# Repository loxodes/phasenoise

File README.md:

# low(ish) phase noise downconverter 
* 10-6000 MHz RF
* DC-1MHz IF
* Internal LO generation, phase locked to RF input
* Designed to fit on the J40 header of Lattice ECP5 EVN eval board

Software development and hardware testing is in progress.
The only documentation is the [schematic](./phase_noise_downconver_schematic_2020_10.pdf).

## Usage
This project is under development, y'all probably don't want to try reproducing it yet.

## License
Unless otherwise noted, all work is under a MIT license.

## Contact
Feel free to contact me at arcticmicrowave@gmail.com or loxodes on irc.freenode.net

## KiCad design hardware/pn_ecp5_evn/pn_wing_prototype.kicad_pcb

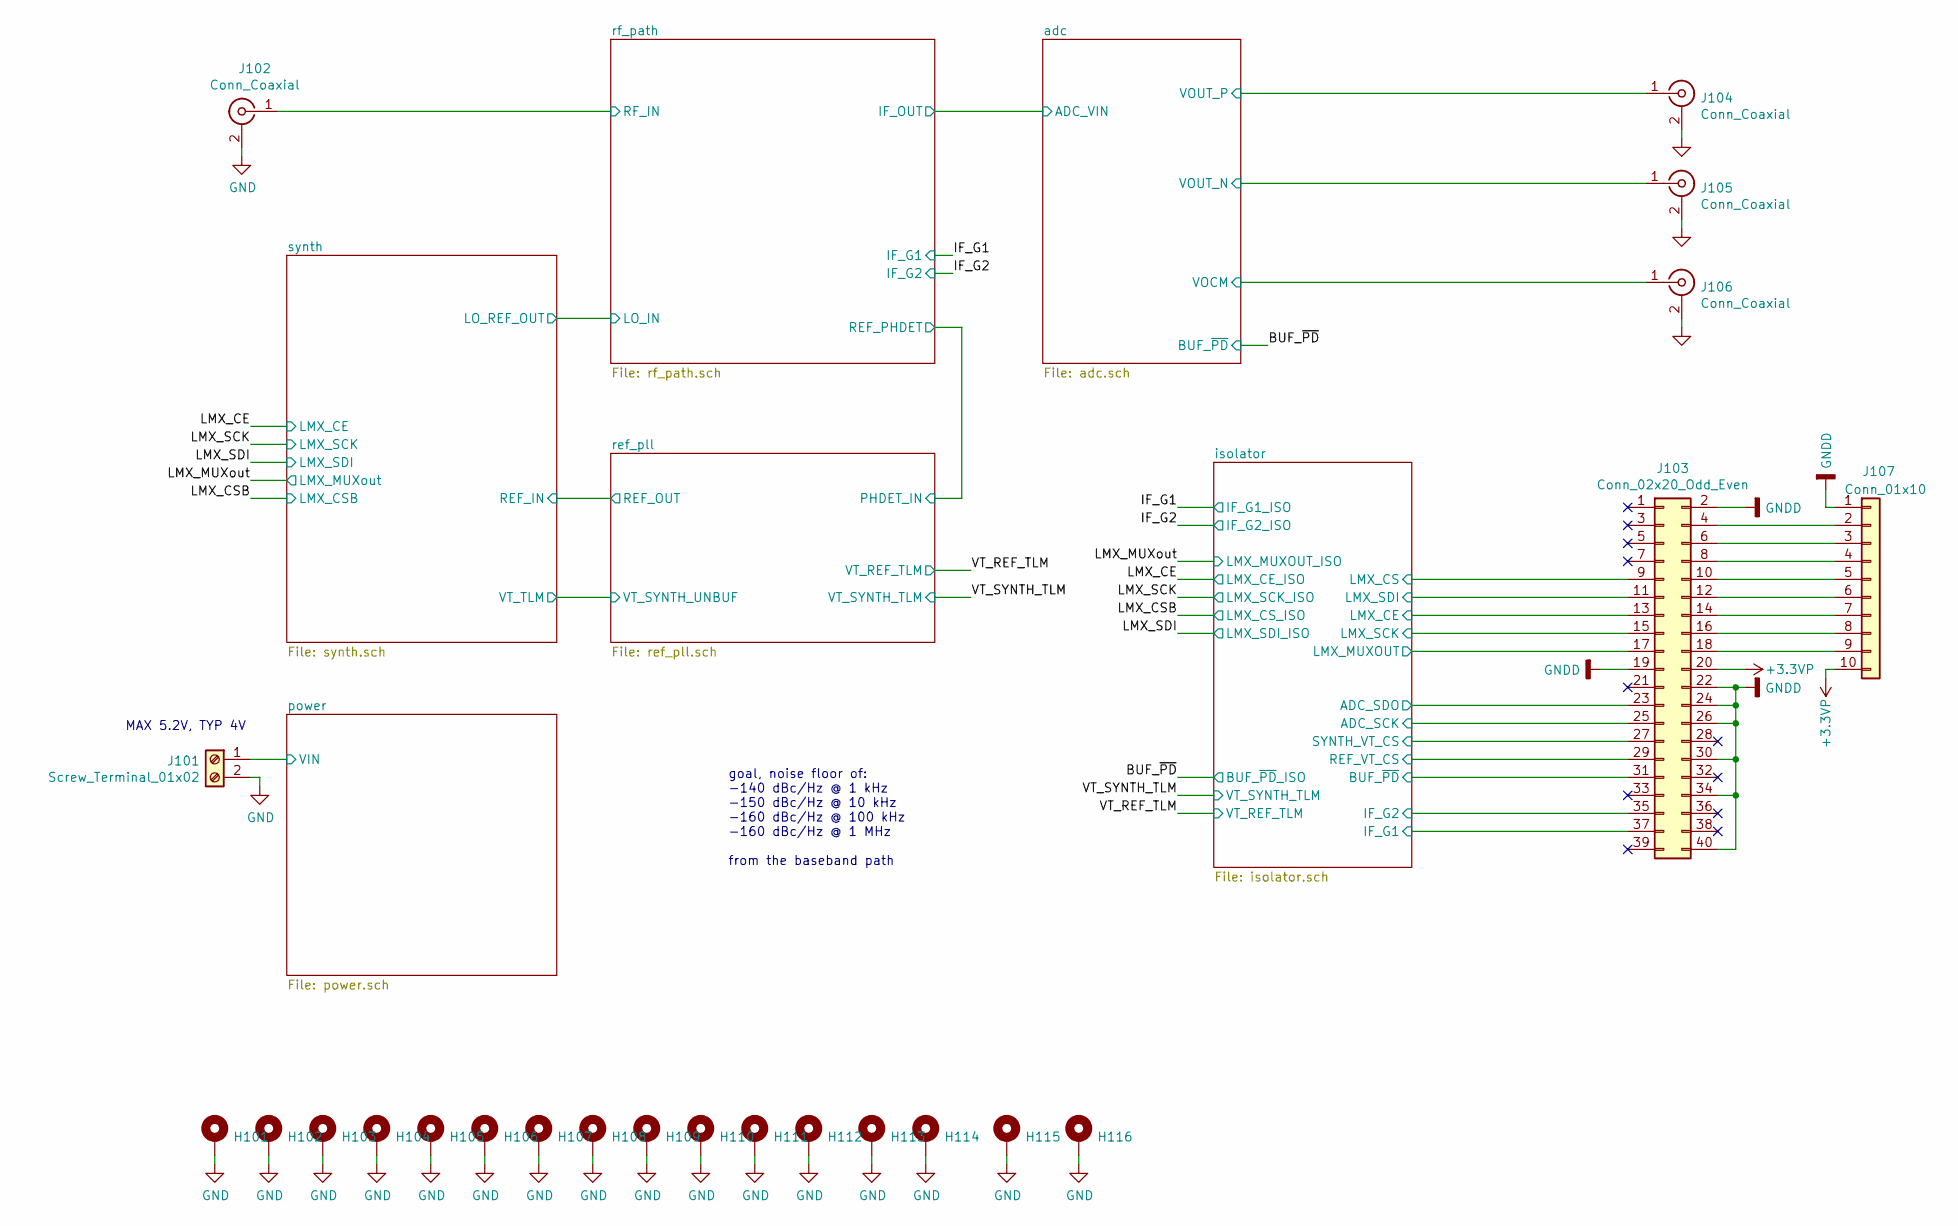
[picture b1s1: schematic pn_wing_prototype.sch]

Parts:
H101, H102, H103, H104, H105, H106, H107, H108, H109, H110, H111, H112, H113, H114, H115, H116: MountingHole_Pad; MountingHole_2.7mm_M2.5_ISO14580_Pad
J101: Screw_Terminal_01x02; TerminalBlock_Phoenix_MPT-0,5-2-2.54_1x02_P2.54mm_Horizontal
J102, J104, J105, J106: Conn_Coaxial; SMA_Molex_73251-1153_OSHFR408
J103: Conn_02x20_Odd_Even; PinSocket_2x20_P2.54mm_Vertical
J107: Conn_01x10; PinHeader_1x10_P2.54mm_Vertical

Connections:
+3.3VP: J103.20, J107.10; also elsewhere on the board
/adc/VOCM: J106.1 (In); also elsewhere on the board
/adc/VOUT_N: J105.1 (In); also elsewhere on the board
/adc/VOUT_P: J104.1 (In); also elsewhere on the board
/isolator/ADC_SCK: J103.25; also elsewhere on the board
/isolator/ADC_SDO: J103.23; also elsewhere on the board
/isolator/BUF_~PD: J103.31; also elsewhere on the board
/isolator/IF_G1: J103.37; also elsewhere on the board
/isolator/IF_G2: J103.35; also elsewhere on the board
/isolator/LMX_CE: J103.13; also elsewhere on the board
/isolator/LMX_CS: J103.9; also elsewhere on the board
/isolator/LMX_MUXOUT: J103.17; also elsewhere on the board
/isolator/LMX_SCK: J103.15; also elsewhere on the board
/isolator/LMX_SDI: J103.11; also elsewhere on the board
/isolator/REF_VT_CS: J103.29; also elsewhere on the board
/isolator/SYNTH_VT_CS: J103.27; also elsewhere on the board
/power/VIN: J101.1; also elsewhere on the board
/rf_path/RF_IN: J102.1 (In); also elsewhere on the board
GND: H101.1, H102.1, H103.1, H104.1, H105.1, H106.1, H107.1, H108.1, H109.1, H110.1, H111.1, H112.1, H113.1, H114.1, H115.1, H116.1, J101.2, J102.2 (Ext), J104.2 (Ext), J105.2 (Ext), J106.2 (Ext); also elsewhere on the board
GNDD: J103.2, J103.19, J103.22, J103.24, J103.26, J103.30, J103.34, J103.40, J107.1; also elsewhere on the board
unnamed: J103.4, J107.2
unnamed: J103.6, J107.3
unnamed: J103.8, J107.4
unnamed: J103.10, J107.5
unnamed: J103.12, J107.6
unnamed: J103.14, J107.7
unnamed: J103.16, J107.8
unnamed: J103.18, J107.9

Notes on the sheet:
goal, noise floor of: -140 dBc/Hz @ 1 kHz -150 dBc/Hz @ 10 kHz -160 dBc/Hz @ 100 kHz -160 dBc/Hz @ 1 MHz from the baseband path
MAX 5.2V, TYP 4V

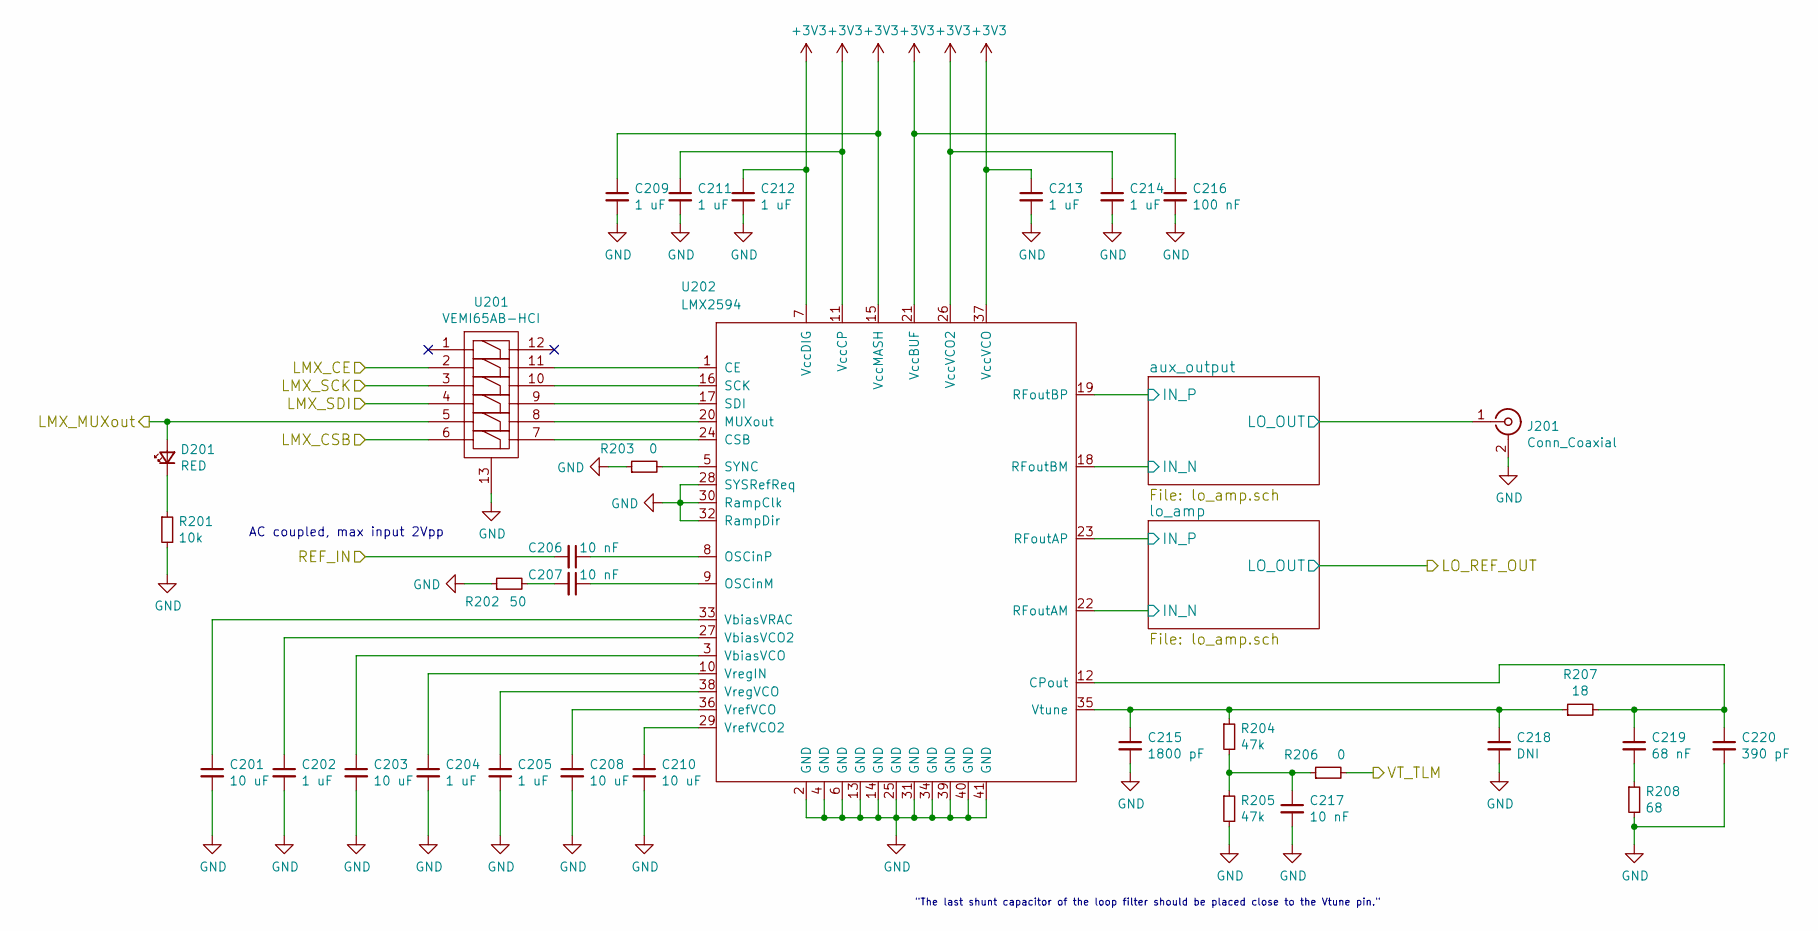
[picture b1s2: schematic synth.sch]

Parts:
C201, C203, C208, C210: 10 uF; C_0603_1608Metric
C202, C204, C205, C209, C211, C212, C213, C214: 1 uF; C_0402_1005Metric
C206, C207, C217: 10 nF; C_0402_1005Metric
C215: 1800 pF; C_0402_1005Metric
C216: 100 nF; C_0402_1005Metric
C218: DNI; C_0603_1608Metric
C219: 68 nF; C_0603_1608Metric
C220: 390 pF; C_0603_1608Metric
D201: RED; LED_0603_1608Metric
J201: Conn_Coaxial; SMA_Molex_73251-1153_OSHFR408
R201: 10k; R_0402_1005Metric
R202: 50; R_0402_1005Metric
R203, R206: 0; R_0402_1005Metric
R204, R205: 47k; R_0402_1005Metric
R207: 18; R_0402_1005Metric
R208: 68; R_0402_1005Metric
U201: VEMI65AB-HCI; LLP2513-13L
U202: LMX2594; Texas_S-PVQFN-N40_EP4.6x4.6mm

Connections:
/LMX_CE: U201.2; also elsewhere on the board
/LMX_CSB: U201.6; also elsewhere on the board
/LMX_MUXout: D201.2 (A), U201.5; also elsewhere on the board
/LMX_SCK: U201.3; also elsewhere on the board
/LMX_SDI: U201.4; also elsewhere on the board
/ref_pll/VT_SYNTH_UNBUF: R206.2; also elsewhere on the board
/synth/REF_IN: C206.2; also elsewhere on the board
/synth/aux_output/IN_N: U202.18 (RFoutBM); also elsewhere on the board
/synth/aux_output/IN_P: U202.19 (RFoutBP); also elsewhere on the board
/synth/aux_output/LO_OUT: J201.1 (In); also elsewhere on the board
/synth/lo_amp/IN_N: U202.22 (RFoutAM); also elsewhere on the board
/synth/lo_amp/IN_P: U202.23 (RFoutAP); also elsewhere on the board
GND: C201.2, C202.2, C203.2, C204.2, C205.2, C208.2, C209.2, C210.2, C211.2, C212.2, C213.2, C214.2, C215.2, C216.2, C217.2, C218.2, C220.2, J201.2 (Ext), R201.2, R202.1, R203.1, R205.2, R208.2, U201.13, U202.2 (GND), U202.4 (GND), U202.6 (GND), U202.13 (GND), U202.14 (GND), U202.25 (GND), U202.28 (SYSRefReq), U202.30 (RampClk), U202.31 (GND), U202.32 (RampDir), U202.34 (GND), U202.39 (GND), U202.40 (GND), U202.41 (GND); also elsewhere on the board
unnamed: C201.1, U202.33 (VbiasVRAC)
unnamed: C202.1, U202.27 (VbiasVCO2)
unnamed: C203.1, U202.3 (VbiasVCO)
unnamed: C204.1, U202.10 (VregIN)
unnamed: C205.1, U202.38 (VregVCO)
unnamed: C206.1, U202.8 (OSCinP)
unnamed: C207.1, U202.9 (OSCinM)
unnamed: C207.2, R202.2
unnamed: C208.1, U202.36 (VrefVCO)
unnamed: C210.1, U202.29 (VrefVCO2)
unnamed: C215.1, C218.1, R204.1, R207.1, U202.35 (Vtune)
unnamed: C217.1, R204.2, R205.1, R206.1
unnamed: C219.1, C220.1, R207.2, U202.12 (CPout)
unnamed: C219.2, R208.1
unnamed: D201.1 (K), R201.1
unnamed: R203.2, U202.5 (SYNC)
unnamed: U201.7, U202.24 (CSB)
unnamed: U201.8, U202.20 (MUXout)
unnamed: U201.9, U202.17 (SDI)
unnamed: U201.10, U202.16 (SCK)
unnamed: U201.11, U202.1 (CE)

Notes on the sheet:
"The last shunt capacitor of the loop filter should be placed close to the Vtune pin."
AC coupled, max input 2Vpp

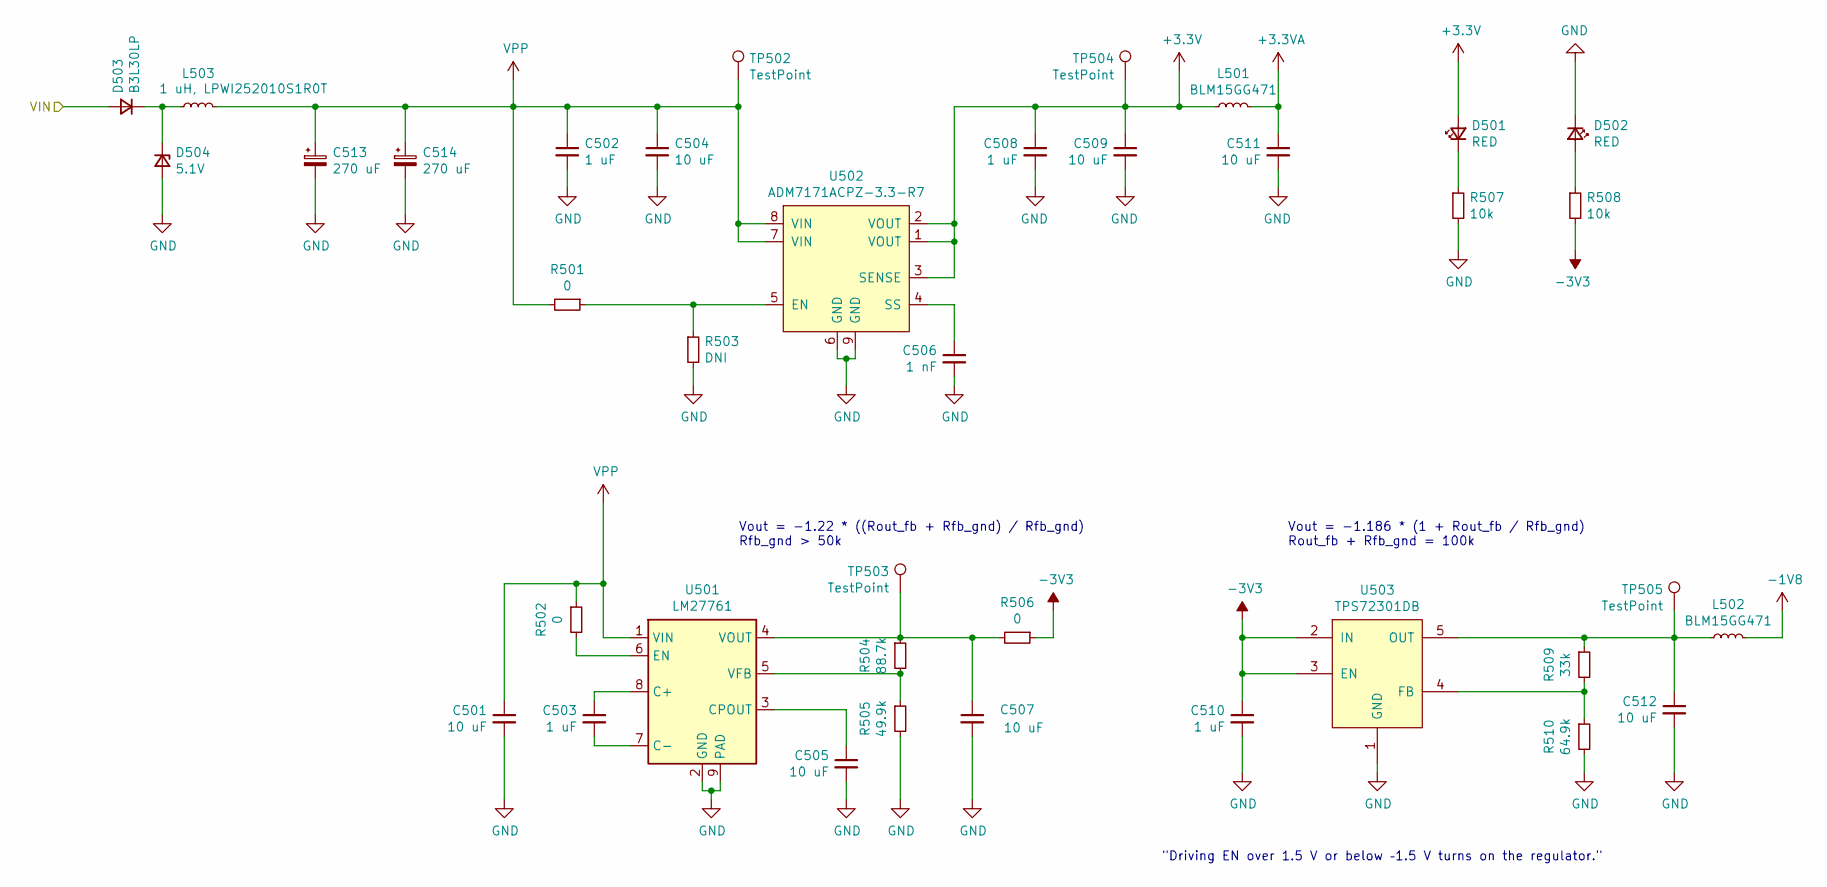
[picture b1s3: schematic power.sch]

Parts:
C501, C504, C505, C507, C509, C511, C512: 10 uF; C_0603_1608Metric
C502, C503, C508, C510: 1 uF; C_0402_1005Metric
C506: 1 nF; C_0402_1005Metric
C513, C514: 270 uF; CP_Elec_6.3x5.9; MPN 875105245014
D501, D502: RED; LED_0603_1608Metric
D503: B3L30LP; AP02002_DFN8_DIODE
D504: 5.1V; D_SOD-323
L501, L502: BLM15GG471; L_0402_1005Metric
L503: 1 uH, LPWI252010S1R0T; L_1008_2520Metric
R501, R502, R506: 0; R_0402_1005Metric
R503: DNI; R_0402_1005Metric
R504: 88.7k; R_0402_1005Metric
R505: 49.9k; R_0402_1005Metric
R507, R508: 10k; R_0402_1005Metric
R509: 33k; R_0402_1005Metric
R510: 64.9k; R_0402_1005Metric
TP502, TP503, TP504, TP505: TestPoint; TestPoint_Keystone_5015_Micro-Minature
U501: LM27761; WSON-8-1EP_2x2mm_P0.5mm_EP0.9x1.6mm
U502: ADM7171ACPZ-3.3-R7; DFN-8-1EP_3x3mm_P0.5mm_EP1.66x2.38mm
U503: TPS72301DB; SOT-23-5

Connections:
+3.3VA: C511.1, L501.2
-1V8: L502.2; also elsewhere on the board
-3V3: C510.1, R506.1, R508.2, U503.2 (IN), U503.3 (EN); also elsewhere on the board
/power/VIN: D503.2 (A); also elsewhere on the board
GND: C501.2, C502.2, C504.2, C505.2, C506.2, C507.2, C508.2, C509.2, C510.2, C511.2, C512.2, C513.2, C514.2, D502.1 (K), D504.2 (A), R503.2, R505.2, R507.2, R510.2, U501.2 (GND), U501.9 (PAD), U502.6 (GND), U502.9 (GND), U503.1 (GND); also elsewhere on the board
unnamed: C503.1, U501.8 (C+)
unnamed: C503.2, U501.7 (C-)
unnamed: C505.1, U501.3 (CPOUT)
unnamed: C506.1, U502.4 (SS)
unnamed: C507.1, R504.1, R506.2, TP503.1, U501.4 (VOUT)
unnamed: C512.1, L502.1, R509.1, TP505.1, U503.5 (OUT)
unnamed: D501.1 (K), R507.1
unnamed: D502.2 (A), R508.1
unnamed: D503.1 (K), D504.1 (K), L503.1
unnamed: R501.1, R503.1, U502.5 (EN)
unnamed: R502.2, U501.6 (EN)
unnamed: R504.2, R505.1, U501.5 (VFB)
unnamed: R509.2, R510.1, U503.4 (FB)
VPP: C501.1, C502.1, C504.1, C513.1, C514.1, L503.2, R501.2, R502.1, TP502.1, U501.1 (VIN), U502.7 (VIN), U502.8 (VIN)

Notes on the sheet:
Vout = -1.186 * (1 + Rout_fb / Rfb_gnd) Rout_fb + Rfb_gnd = 100k
Vout = -1.22 * ((Rout_fb + Rfb_gnd) / Rfb_gnd) Rfb_gnd > 50k
"Driving EN over 1.5 V or below –1.5 V turns on the regulator."

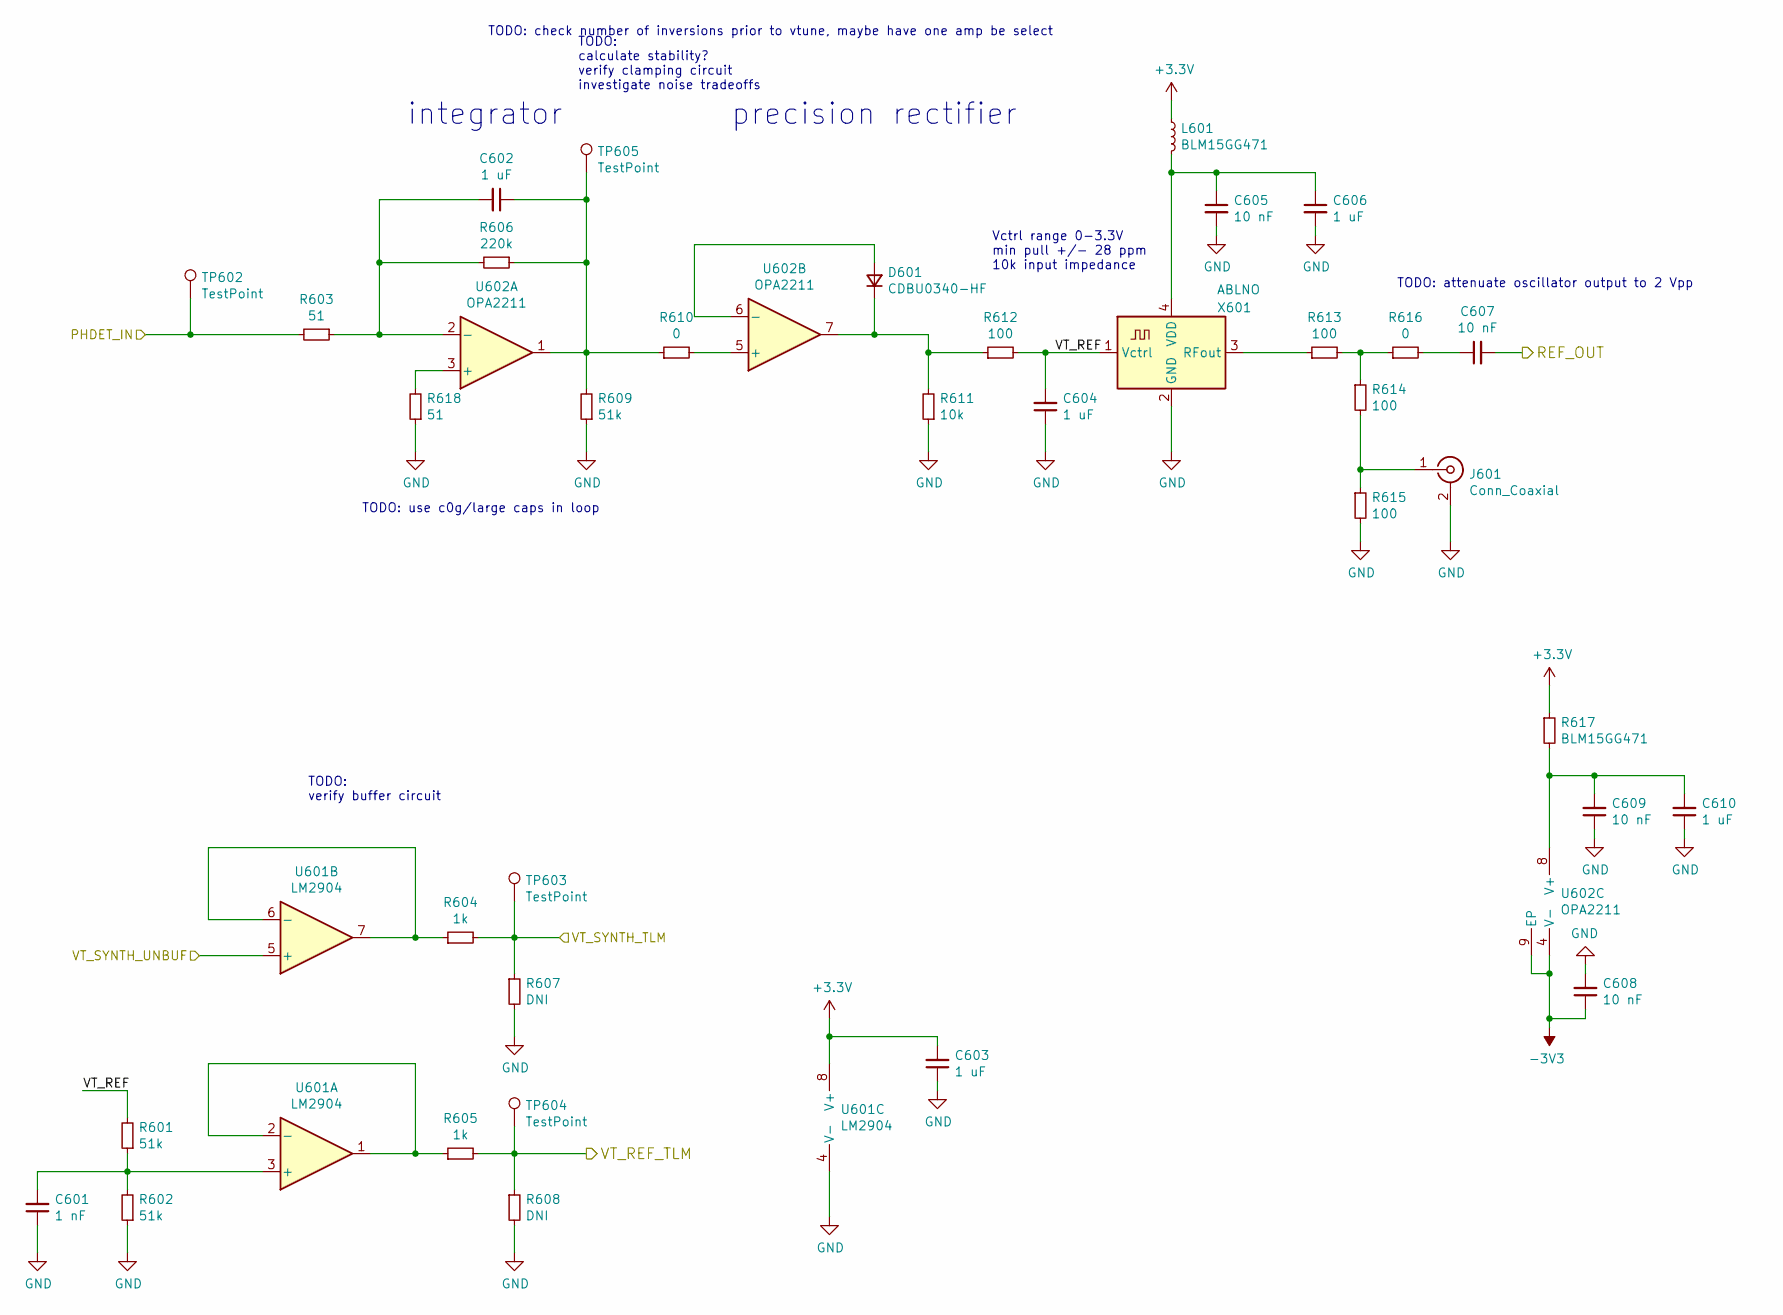
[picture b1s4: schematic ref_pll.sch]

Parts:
C601: 1 nF; C_0402_1005Metric
C602, C604: 1 uF; C_0603_1608Metric
C603, C606, C610: 1 uF; C_0402_1005Metric
C605, C607, C608, C609: 10 nF; C_0402_1005Metric
D601: CDBU0340-HF; D_0603_1608Metric
J601: Conn_Coaxial; U.FL_Hirose_U.FL-R-SMT-1_Vertical
L601: BLM15GG471; L_0402_1005Metric
R601, R602, R609: 51k; R_0402_1005Metric
R603, R618: 51; R_0402_1005Metric
R604, R605: 1k; R_0402_1005Metric
R606: 220k; R_0402_1005Metric
R607, R608: DNI; R_0402_1005Metric
R610, R616: 0; R_0402_1005Metric
R611: 10k; R_0402_1005Metric
R612, R613, R614, R615: 100; R_0402_1005Metric
R617: BLM15GG471; R_0402_1005Metric
TP602, TP603, TP604, TP605: TestPoint; TestPoint_Keystone_5015_Micro-Minature
U601: LM2904; MSOP-8_3x3mm_P0.65mm
U602: OPA2211; SOIC-8-1EP_3.9x4.9mm_P1.27mm_EP2.514x3.2mm
X601: ABLNO; Oscillator_SMD_Abracon_ABLNO

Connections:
-3V3: C608.1, U602.4 (V-), U602.9 (EP); also elsewhere on the board
/VT_REF_TLM: R605.2, R608.1, TP604.1; also elsewhere on the board
/VT_SYNTH_TLM: R604.2, R607.1, TP603.1; also elsewhere on the board
/ref_pll/PHDET_IN: R603.2, TP602.1; also elsewhere on the board
/ref_pll/VT_REF: C604.2, R601.2, R612.2, X601.1 (Vctrl)
/ref_pll/VT_SYNTH_UNBUF: U601.5 (+); also elsewhere on the board
/synth/REF_IN: C607.2; also elsewhere on the board
GND: C601.1, C603.1, C604.1, C605.2, C606.2, C608.2, C609.1, C610.1, J601.2 (Ext), R602.1, R607.2, R608.2, R609.1, R611.1, R615.2, R618.1, U601.4 (V-), X601.2 (GND); also elsewhere on the board
unnamed: C601.2, R601.1, R602.2, U601.3 (+)
unnamed: C602.1, R606.1, R609.2, R610.1, TP605.1, U602.1
unnamed: C602.2, R603.1, R606.2, U602.2 (-)
unnamed: C605.1, C606.1, L601.2, X601.4 (VDD)
unnamed: C607.1, R616.2
unnamed: C609.2, C610.2, R617.2, U602.8 (V+)
unnamed: D601.1 (K), R611.2, R612.1, U602.7
unnamed: D601.2 (A), U602.6 (-)
unnamed: J601.1 (In), R614.2, R615.1
unnamed: R604.1, U601.6 (-), U601.7
unnamed: R605.1, U601.1, U601.2 (-)
unnamed: R610.2, U602.5 (+)
unnamed: R613.1, X601.3 (RFout)
unnamed: R613.2, R614.1, R616.1
unnamed: R618.2, U602.3 (+)

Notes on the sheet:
Vctrl range 0-3.3V min pull +/- 28 ppm 10k input impedance
TODO: calculate stability? verify clamping circuit investigate noise tradeoffs
TODO: verify buffer circuit
TODO: check number of inversions prior to vtune, maybe have one amp be select
integrator
precision rectifier
TODO: attenuate oscillator output to 2 Vpp
TODO: use c0g/large caps in loop

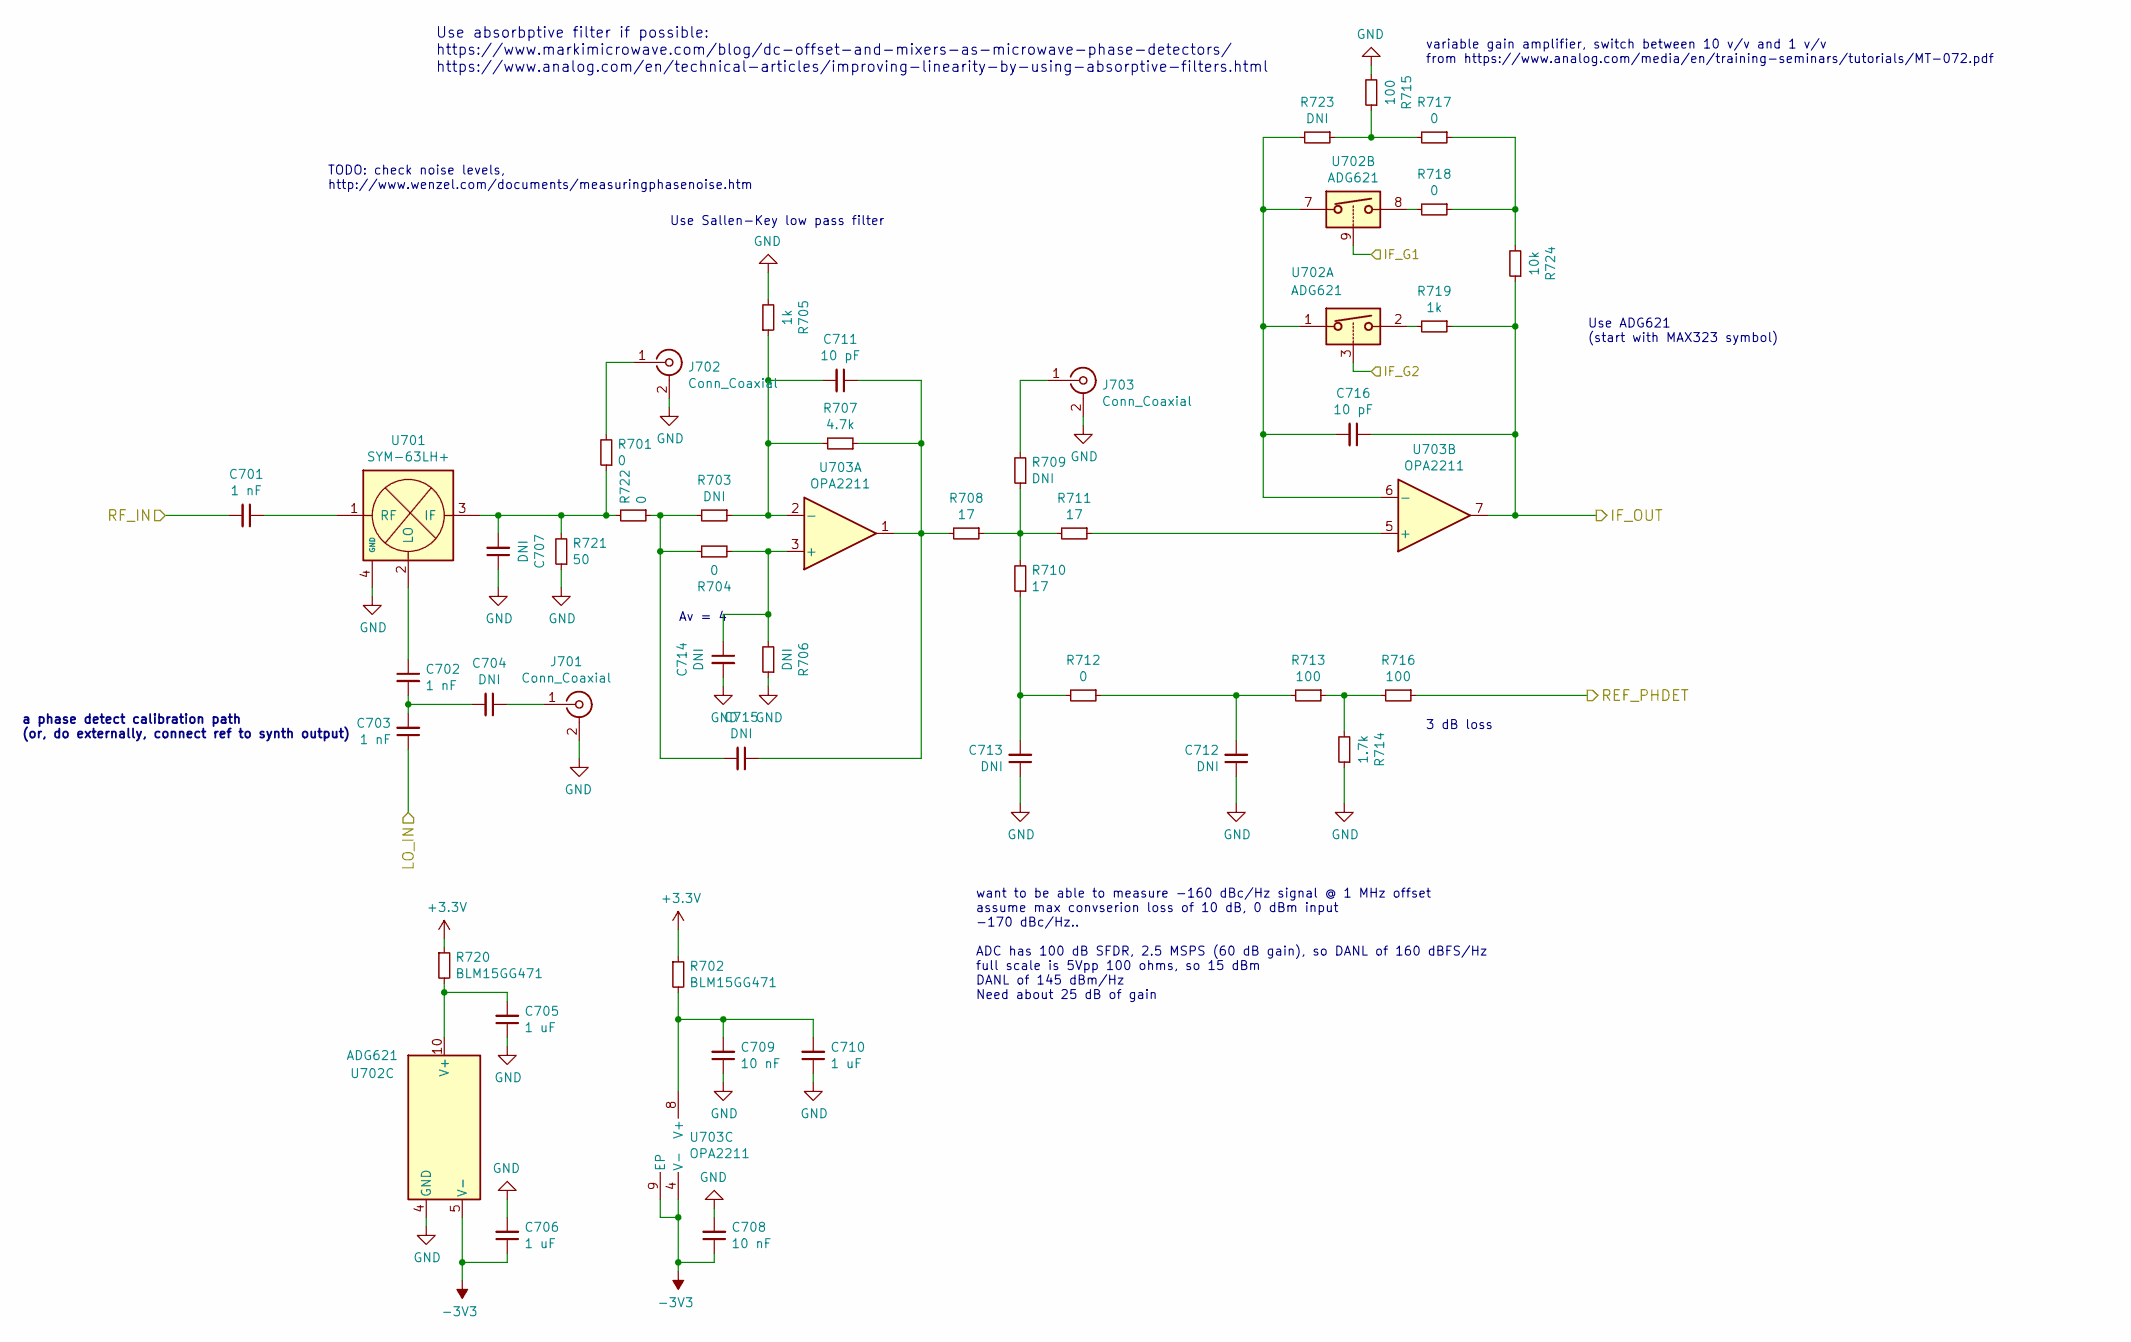
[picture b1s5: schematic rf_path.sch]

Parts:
C701, C702, C703: 1 nF; C_0402_1005Metric
C704, C707, C712, C713: DNI; C_0402_1005Metric
C705, C706, C710: 1 uF; C_0402_1005Metric
C708, C709: 10 nF; C_0402_1005Metric
C711, C716: 10 pF; C_0603_1608Metric
C714, C715: DNI; C_0603_1608Metric
J701, J702, J703: Conn_Coaxial; U.FL_Hirose_U.FL-R-SMT-1_Vertical
R701, R704, R712, R717, R718, R722: 0; R_0402_1005Metric
R702, R720: BLM15GG471; R_0402_1005Metric
R703, R706, R709, R723: DNI; R_0402_1005Metric
R705, R719: 1k; R_0402_1005Metric
R707: 4.7k; R_0402_1005Metric
R708, R710, R711: 17; R_0402_1005Metric
R713, R715, R716: 100; R_0402_1005Metric
R714: 1.7k; R_0402_1005Metric
R721: 50; R_0402_1005Metric
R724: 10k; R_0402_1005Metric
U701: SYM-63LH+; Mini-Circuits_TTT167
U702: ADG621; MSOP-10_3x3mm_P0.5mm
U703: OPA2211; SOIC-8-1EP_3.9x4.9mm_P1.27mm_EP2.514x3.2mm

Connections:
-3V3: C706.1, C708.1, U702.5 (V-), U703.4 (V-), U703.9 (EP); also elsewhere on the board
/IF_G1: U702.9; also elsewhere on the board
/IF_G2: U702.3; also elsewhere on the board
/adc/ADC_VIN: C716.1, R719.1, R724.1, U703.7; also elsewhere on the board
/ref_pll/PHDET_IN: R716.1; also elsewhere on the board
/rf_path/LO_IN: C703.1; also elsewhere on the board
/rf_path/RF_IN: C701.2; also elsewhere on the board
GND: C705.1, C706.2, C707.1, C708.2, C709.1, C710.1, C712.1, C713.1, C714.2, J701.2 (Ext), J702.2 (Ext), J703.2 (Ext), R705.2, R706.1, R714.1, R715.2, R721.1, U701.4 (GND), U701.5 (GND), U701.6 (GND), U702.4 (GND); also elsewhere on the board
unnamed: C701.1, U701.1 (RF)
unnamed: C702.1, U701.2 (LO)
unnamed: C702.2, C703.2, C704.2
unnamed: C704.1, J701.1 (In)
unnamed: C705.2, R720.2, U702.10 (V+)
unnamed: C707.2, R701.1, R721.2, R722.2, U701.3 (IF)
unnamed: C709.2, C710.2, R702.2, U703.8 (V+)
unnamed: C711.1, C715.1, R707.1, R708.2, U703.1
unnamed: C711.2, R703.1, R705.1, R707.2, U703.2 (-)
unnamed: C712.2, R712.1, R713.2
unnamed: C713.2, R710.1, R712.2
unnamed: C714.1, R704.2, R706.2, U703.3 (+)
unnamed: C715.2, R703.2, R704.1, R722.1
unnamed: C716.2, R723.2, U702.1, U702.7, U703.6 (-)
unnamed: J702.1 (In), R701.2
unnamed: J703.1 (In), R709.2
unnamed: R708.1, R709.1, R710.2, R711.2
unnamed: R711.1, U703.5 (+)
unnamed: R713.1, R714.2, R716.2
unnamed: R715.1, R717.2, R723.1
unnamed: R717.1, R718.1, R724.2
unnamed: R718.2, U702.8
unnamed: R719.2, U702.2

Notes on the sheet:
Use absorbptive filter if possible: https://www.markimicrowave.com/blog/dc-offset-and-mixers-as-microwave-phase-detectors/ https://www.analog.com/en/technical-articles/improving-linearity-by-using-absorptive-filters.html
TODO: check noise levels, http://www.wenzel.com/documents/measuringphasenoise.htm
a phase detect calibration path (or, do externally, connect ref to synth output)
3 dB loss
Av = 4
want to be able to measure -160 dBc/Hz signal @ 1 MHz offset assume max convserion loss of 10 dB, 0 dBm input -170 dBc/Hz.. ADC has 100 dB SFDR, 2.5 MSPS (60 dB gain), so DANL of 160 dBFS/Hz full scale is 5Vpp 100 ohms, so 15 dBm DANL of 145 dBm/Hz Need about 25 dB of gain
variable gain amplifier, switch between 10 v/v and 1 v/v from https://www.analog.com/media/en/training-seminars/tutorials/MT-072.pdf
Use ADG621 (start with MAX323 symbol)
Use Sallen-Key low pass filter

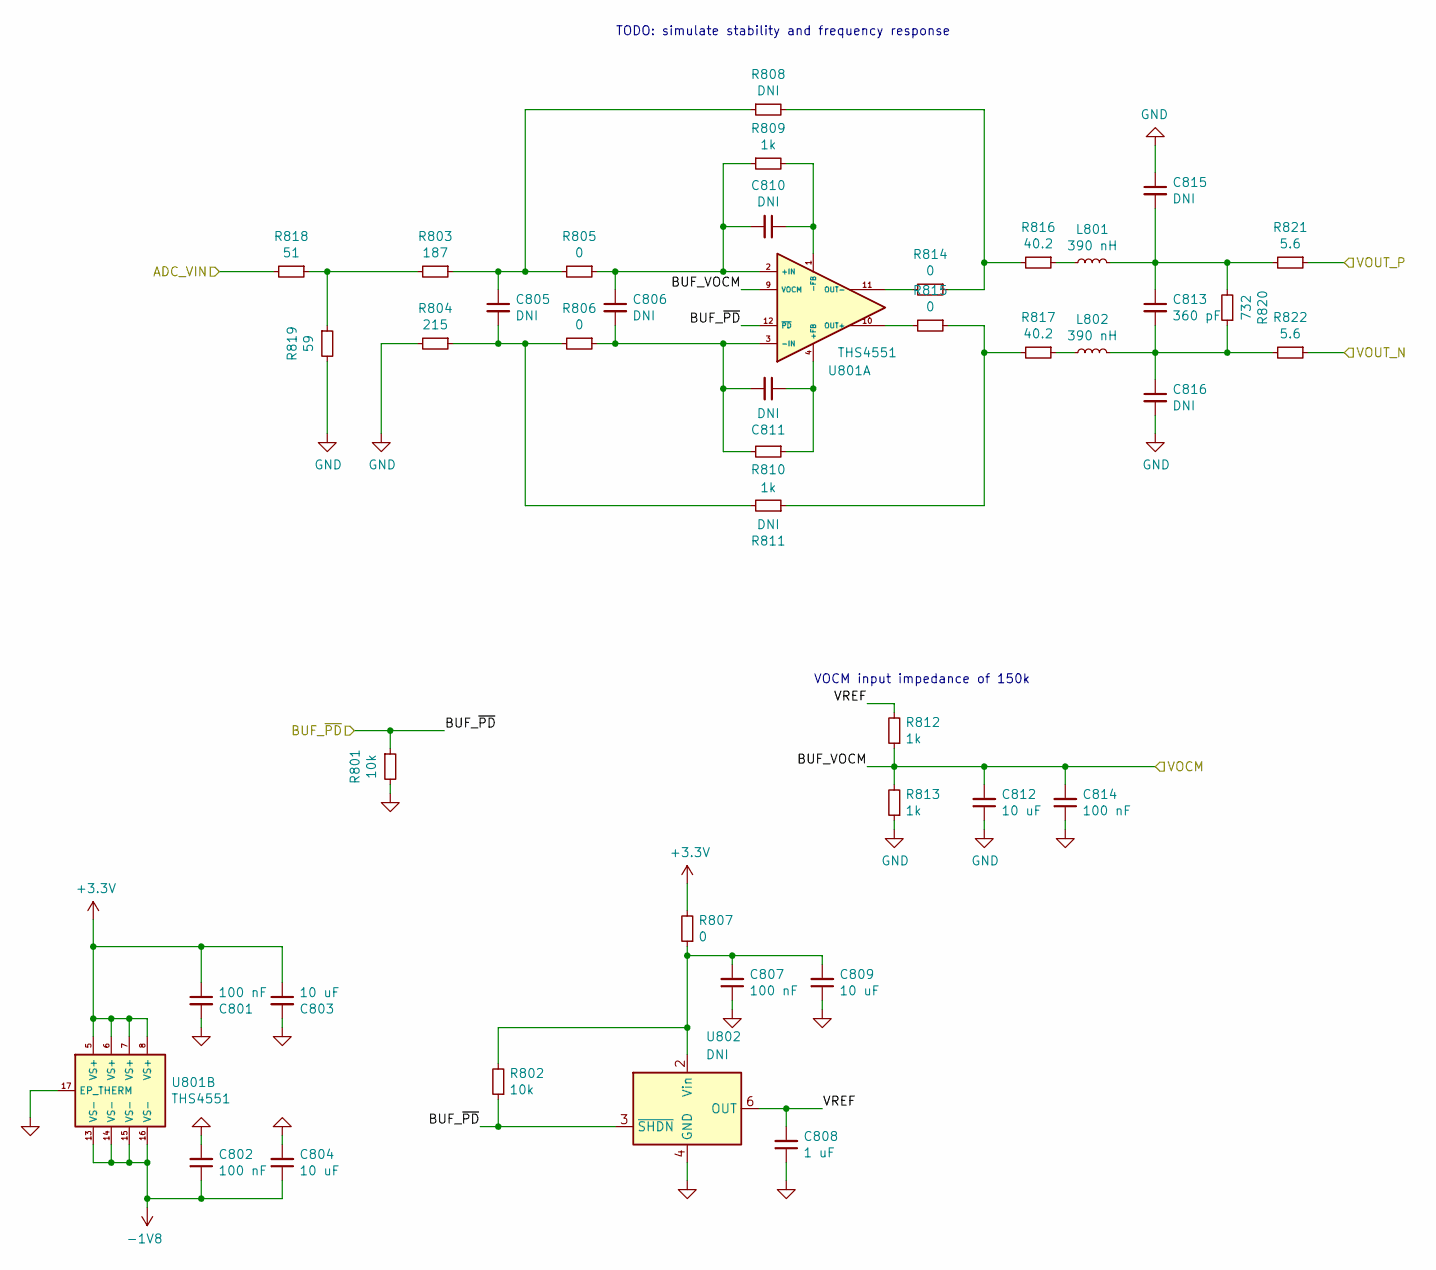
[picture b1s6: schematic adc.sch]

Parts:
C801, C802, C807, C814: 100 nF; C_0402_1005Metric
C803, C804, C809, C812: 10 uF; C_0603_1608Metric
C805, C810, C811: DNI; C_0603_1608Metric
C806, C815, C816: DNI; C_0402_1005Metric
C808: 1 uF; C_0402_1005Metric
C813: 360 pF; C_0402_1005Metric
L801, L802: 390 nH; L_0603_1608Metric
R801, R802: 10k; R_0402_1005Metric
R803: 187; R_0402_1005Metric
R804: 215; R_0402_1005Metric
R805, R806, R807, R814, R815: 0; R_0402_1005Metric
R808, R811: DNI; R_0402_1005Metric
R809, R810, R812, R813: 1k; R_0402_1005Metric
R816, R817: 40.2; R_0402_1005Metric
R818: 51; R_0402_1005Metric
R819: 59; R_0402_1005Metric
R820: 732; R_0402_1005Metric
R821, R822: 5.6; R_0402_1005Metric
U801: THS4551; VQFN-16-1EP_3x3mm_P0.5mm_EP1.6x1.6mm
U802: DNI; MSOP-8_3x3mm_P0.65mm

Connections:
-1V8: C802.1, C804.1, U801.13 (VS-), U801.14 (VS-), U801.15 (VS-), U801.16 (VS-); also elsewhere on the board
/BUF_~PD: R801.1, R802.1, U801.12 (~PD), U802.3 (~SHDN); also elsewhere on the board
/adc/ADC_VIN: R818.2; also elsewhere on the board
/adc/VOCM: C812.2, C814.2, R812.1, R813.2, U801.9 (VOCM); also elsewhere on the board
/adc/VOUT_N: R822.1; also elsewhere on the board
/adc/VOUT_P: R821.1; also elsewhere on the board
/adc/VREF: C808.2, R812.2, U802.6 (OUT)
GND: C801.2, C802.2, C803.2, C804.2, C807.1, C808.1, C809.1, C812.1, C814.1, C815.1, C816.2, R801.2, R804.2, R813.1, R819.2, U801.17 (EP_THERM), U802.4 (GND); also elsewhere on the board
unnamed: C805.1, R803.1, R805.2, R808.1
unnamed: C805.2, R804.1, R806.2, R811.2
unnamed: C806.1, C810.2, R805.1, R809.1, U801.2 (+IN)
unnamed: C806.2, C811.2, R806.1, R810.2, U801.3 (-IN)
unnamed: C807.2, C809.2, R802.2, R807.1, U802.2 (Vin)
unnamed: C810.1, R809.2, U801.1 (-FB)
unnamed: C811.1, R810.1, U801.4 (+FB)
unnamed: C813.1, C815.2, L801.2, R820.2, R821.2
unnamed: C813.2, C816.1, L802.2, R820.1, R822.2
unnamed: L801.1, R816.1
unnamed: L802.1, R817.1
unnamed: R803.2, R818.1, R819.1
unnamed: R808.2, R814.1, R816.2
unnamed: R811.1, R815.1, R817.2
unnamed: R814.2, U801.11 (OUT-)
unnamed: R815.2, U801.10 (OUT+)

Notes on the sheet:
VOCM input impedance of 150k
TODO: simulate stability and frequency response

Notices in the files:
software/ecp5_evn.py:
This file is Copyright (c) 2019 Arnaud Durand <arnaud.durand@unifr.ch>
License: BSD
